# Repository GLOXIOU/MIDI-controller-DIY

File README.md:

# MIDI-controller-DIY

A DIY project for a MIDI controller designed to control lights, featuring knobs, faders, and buttons.

The project is designed to manage stage lighting systems with up to 10 faders, including a master one, 20 keyboard keys, 10 potards, and 3 rotary encoders.

The goal is to not pay hundreds of dollars for an already existing product, and learn! MIDI controller DIY is also intended to be a hardware platform for a future open-source lighting-control system.

---

## Features

* 20 usable keyboard keys
* 10 faders
* 10 potards
* 3 rotary encoders
* USB-C Output
* Compatibility with all lighting control systems via MIDI
* You can also use it as an instrument or anything else
* Compact and portable design
* Designed for DIY assembly and reproduction
* Low-cost hardware

And the design is made to be upgradable/updatable easily if necessary, so it will be able to last over time.

---

## Architecture

The ESP32-S3 is the central processor of the system. It handles USB-C communication and MIDI processing. To connect the ESP32 with all of the 43 components, there are 2 MUX units at the right of the box. 43 buttons, faders, etc., are fully customizable and you can use them as you want.

---

## Hardware and BOM

The current design uses the following main components:

| Component | Quantity | Price |
| --- | --- | --- |
| [Kailh Choc V1 1350](https://fr.aliexpress.com/item/1005012826040037.html?spm=a2g0o.cart.0.0.478d378dYODNq0&mp=1&pdp_npi=6%40dis%21USD%21USD%205.36%21USD%204.93%21%21USD%204.93%21%21%21%40210384a717913205885618903e10fc%2112000059425505100%21ct%21FR%218054027548%21%212%210%21&gatewayAdapt=glo2fra) | 20 | 9.86$ |
| [RV09 B10K 9 mm vertical](https://fr.aliexpress.com/item/1005005951601744.html?spm=a2g0o.productlist.main.2.6a013a5dBfqj0c&algo_pvid=9dd7ff78-7cef-4815-a249-9f4bb1d433f4&algo_exp_id=9dd7ff78-7cef-4815-a249-9f4bb1d433f4-1&pdp_ext_f=%7B%22order%22%3A%22197%22%2C%22eval%22%3A%221%22%2C%22fromPage%22%3A%22search%22%7D&pdp_npi=6%40dis%21USD%217.66%217.66%21%21%2151.02%2151.02%21%4021613be817921531317277993e10c3%2112000034999053530%21sea%21FR%218054027548%21X%211%210%21n_tag%3A-29911%3Bd%3A8484f755%3Bm03_new_user%3A-29895&curPageLogUid=b76fqSVCkx9n&utparam-url=scene%3Asearch%7Cquery_from%3A%7Cx_object_id%3A1005005951601744%7C_p_origin_prod%3A) | 10 | 7.90$ |
| [EC11 through-hole with push-button, 20 mm shaft](https://fr.aliexpress.com/item/1005009889978797.html?spm=a2g0o.cart.0.0.478d378dYODNq0&mp=1&pdp_npi=6%40dis%21USD%21USD%205.88%21USD%202.68%21%21USD%202.68%21%21%21%40210384a717913207470334482e10fc%2112000050490958429%21ct%21FR%218054027548%21%212%210%21&gatewayAdapt=glo2fra) | 3 | 5.36$ |
| [CD4067BE in DIP-24](https://fr.aliexpress.com/item/1005011580802574.html?spm=a2g0o.cart.0.0.478d378dYODNq0&mp=1&pdp_npi=6%40dis%21USD%21USD%206.69%21USD%206.69%21%21USD%206.69%21%21%21%40210384a717913207470334482e10fc%2112000055976316177%21ct%21FR%218054027548%21%211%210%21&gatewayAdapt=glo2fra) | 2 | 6.69$ |
| [1N4148 diodes](https://fr.aliexpress.com/item/4000142272546.html?spm=a2g0o.cart.0.0.478d378dYODNq0&mp=1&pdp_npi=6%40dis%21USD%21USD+1.64%21USD+1.64%21%21USD+1.64%21%21%21%40210384a717913207470334482e10fc%2110000000428321629%21ct%21FR%218054027548%21%211%210%21&pdp_ext_f=%7B%22cart2PdpParams%22%3A%7B%22pdpBusinessMode%22%3A%22retail%22%7D%7D&gatewayAdapt=glo2fra) | 20 | 1.64$ |
| [faders SC6021N 10k](https://fr.aliexpress.com/item/1005007799302164.html?spm=a2g0o.productlist.main.1.25616b84d4WSxL&algo_pvid=9953769d-b040-40bf-b6fd-b3c135a11ea9&algo_exp_id=9953769d-b040-40bf-b6fd-b3c135a11ea9-0&pdp_ext_f=%7B%22order%22%3A%22247%22%2C%22spu_best_type%22%3A%22price%22%2C%22eval%22%3A%221%22%2C%22fromPage%22%3A%22search%22%7D&pdp_npi=6%40dis%21USD%212.25%212.25%21%21%2115.00%2115.00%21%400b88486a17915615343565643e0f22%2112000042240271501%21sea%21FR%218054027548%21X%211%210%21n_tag%3A-29911%3Bd%3A8484f755%3Bm03_new_user%3A-29895&curPageLogUid=HQigGaQEblGd&utparam-url=scene%3Asearch%7Cquery_from%3A%7Cx_object_id%3A1005007799302164%7C_p_origin_prod%3A) | 10 | 9$ |
| [ESP32-S3 N16R8](https://fr.aliexpress.com/item/1005008809316571.html?spm=a2g0o.cart.0.0.478d378dYODNq0&mp=1&pdp_npi=6%40dis%21USD%21USD+8.02%21USD+8.02%21%21USD+8.02%21%21%21%40210384a717913207470334482e10fc%2112000046760012013%21ct%21FR%218054027548%21%211%210%21&pdp_ext_f=%7B%22cart2PdpParams%22%3A%7B%22pdpBusinessMode%22%3A%22retail%22%7D%7D&gatewayAdapt=glo2fra) | 1 | 8.02$ |
| [Knobs cap](https://fr.aliexpress.com/item/1005012925297636.html?spm=a2g0o.productlist.main.3.703f7c3epPU0Mz&algo_pvid=4c36b13e-f743-447c-8d31-d169bc98973d&algo_exp_id=4c36b13e-f743-447c-8d31-d169bc98973d-2&pdp_ext_f=%7B%22order%22%3A%2243%22%2C%22spu_best_type%22%3A%22price%22%2C%22eval%22%3A%221%22%2C%22fromPage%22%3A%22search%22%7D&pdp_npi=6%40dis%21USD%211.88%212.68%21%21%2112.52%2117.86%21%40210384a717915626045184749e0d20%2112000059797212246%21sea%21FR%218054027548%21X%211%210%21n_tag%3A-29911%3Bd%3A8484f755%3Bm03_new_user%3A-29895&curPageLogUid=mtFiF5q8pKs0&utparam-url=scene%3Asearch%7Cquery_from%3A%7Cx_object_id%3A1005012925297636%7C_p_origin_prod%3A) | 10 | 2.68$ |
| [PCB](https://jlcpcb.com/) | 1 | 16,60$ |
| [Lowprofile keycaps](https://fr.aliexpress.com/item/1005006624568390.html?spm=a2g0o.productlist.main.39.7ada7cc1xmwatk&algo_pvid=869ea550-58a6-4ce8-a4f5-cac4802f06d0&algo_exp_id=869ea550-58a6-4ce8-a4f5-cac4802f06d0-36&pdp_ext_f=%7B%22order%22%3A%2288%22%2C%22eval%22%3A%221%22%2C%22fromPage%22%3A%22search%22%7D&pdp_npi=6%40dis%21USD%218.67%218.67%21%21%2157.76%2157.76%21%402103849717915626622064135e13a7%2112000037855001108%21sea%21FR%218054027548%21X%211%210%21n_tag%3A-29911%3Bd%3A8484f755%3Bm03_new_user%3A-29895&curPageLogUid=p3pCjUj8SJOC&utparam-url=scene%3Asearch%7Cquery_from%3A%7Cx_object_id%3A1005006624568390%7C_p_origin_prod%3A) | 20 | 17.34$ |
| Total | --- | 85.09$ |

The complete component list is available in [BOM.csv](BOM.csv).

---

## Processing and memory

I selected the ESP32-S3 because the project requires a bit of processing power for MIDI handling, though not a huge amount. That’s why it’s better suited for the task than a Raspberry Pi.

It is responsible for:

* MIDI processing
* USB-C Output
* 43 component inputs

All the data, saves, and other settings are stored in the internal storage system of the ESP32.

---

## MIDI

The MIDI controller is designed to support lighting control software like grandMA onPC, QLC+, or others via standard MIDI remote commands.

Each hardware input reads multiple analog faders, push buttons, and encoders through multiplexers or direct GPIO pins on the ESP32.

Standard USB-MIDI and serial communication protocols are used, handled by the hardware USB/UART interfaces on the microcontroller.

The MIDI data rate operates at standard MIDI baud rates or high-speed USB-MIDI.

For example, moving a physical fader transmits a Control Change (CC) message to precisely control lighting playback levels in software.

---

## Components and enclosure

There is a PCB in this project because it's required. Here are all the components included:

* ESP32-S3 x1
* MUX CD4067BE in DIP-24 x2
* Kailh Choc V1 1350 x20
* RV09 B10K 9 mm vertical x10
* EC11 through-hole with push-button x3
* faders SC6021N B10K x10

Here's a screenshot of the PCB with some of the components:

The PCB file is [here](3D-files/PCB.step).
And you can modify it using KiCad with [this](KiCad%20-%20MIDI-controller) folder.

The case is 283mm x 250mm x 60mm, and is designed to perfectly house all components, be easy to install, not take up much space, and be durable.

Here's a look at it:

Assembly file: [assembly-Midi-controller-DIY.step](3D-files/assembly-Midi-controller-DIY.step)  
Print file: [to print](3D-files/to%20print/)

---

## Estimated cost

The current estimate is $85.09 of components.
This does not include assembly, enclosure parts, future design changes, or the print filament that I already have.

---

## Project journal

The development process is documented in [JOURNAL.md](JOURNAL.md).

It includes in-depth design, configuration, part of the code, enclosure design, BOM creation, and the problems encountered during development.

---

## Inspiration and credits

The MIDI Controller DIY project was inspired by the GrandMa Wing.

The MIDI Controller DIY is an independent design developed from this inspiration.

Credits:
* GrandMa Wing — inspiration for the project concept and overall goal of creating an affordable MIDI interface.
* GrabCAD community — some 3D component models were used as reference geometry for the CAD assembly. The original authors retain ownership of their respective models:
  * ESP32-S3
  * MUX CD4067BE in DIP-24
  * Kailh Choc V1 1350
  * RV09 B10K 9 mm vertical
  * EC11 through-hole with push-button
  * faders SC1009G B10K

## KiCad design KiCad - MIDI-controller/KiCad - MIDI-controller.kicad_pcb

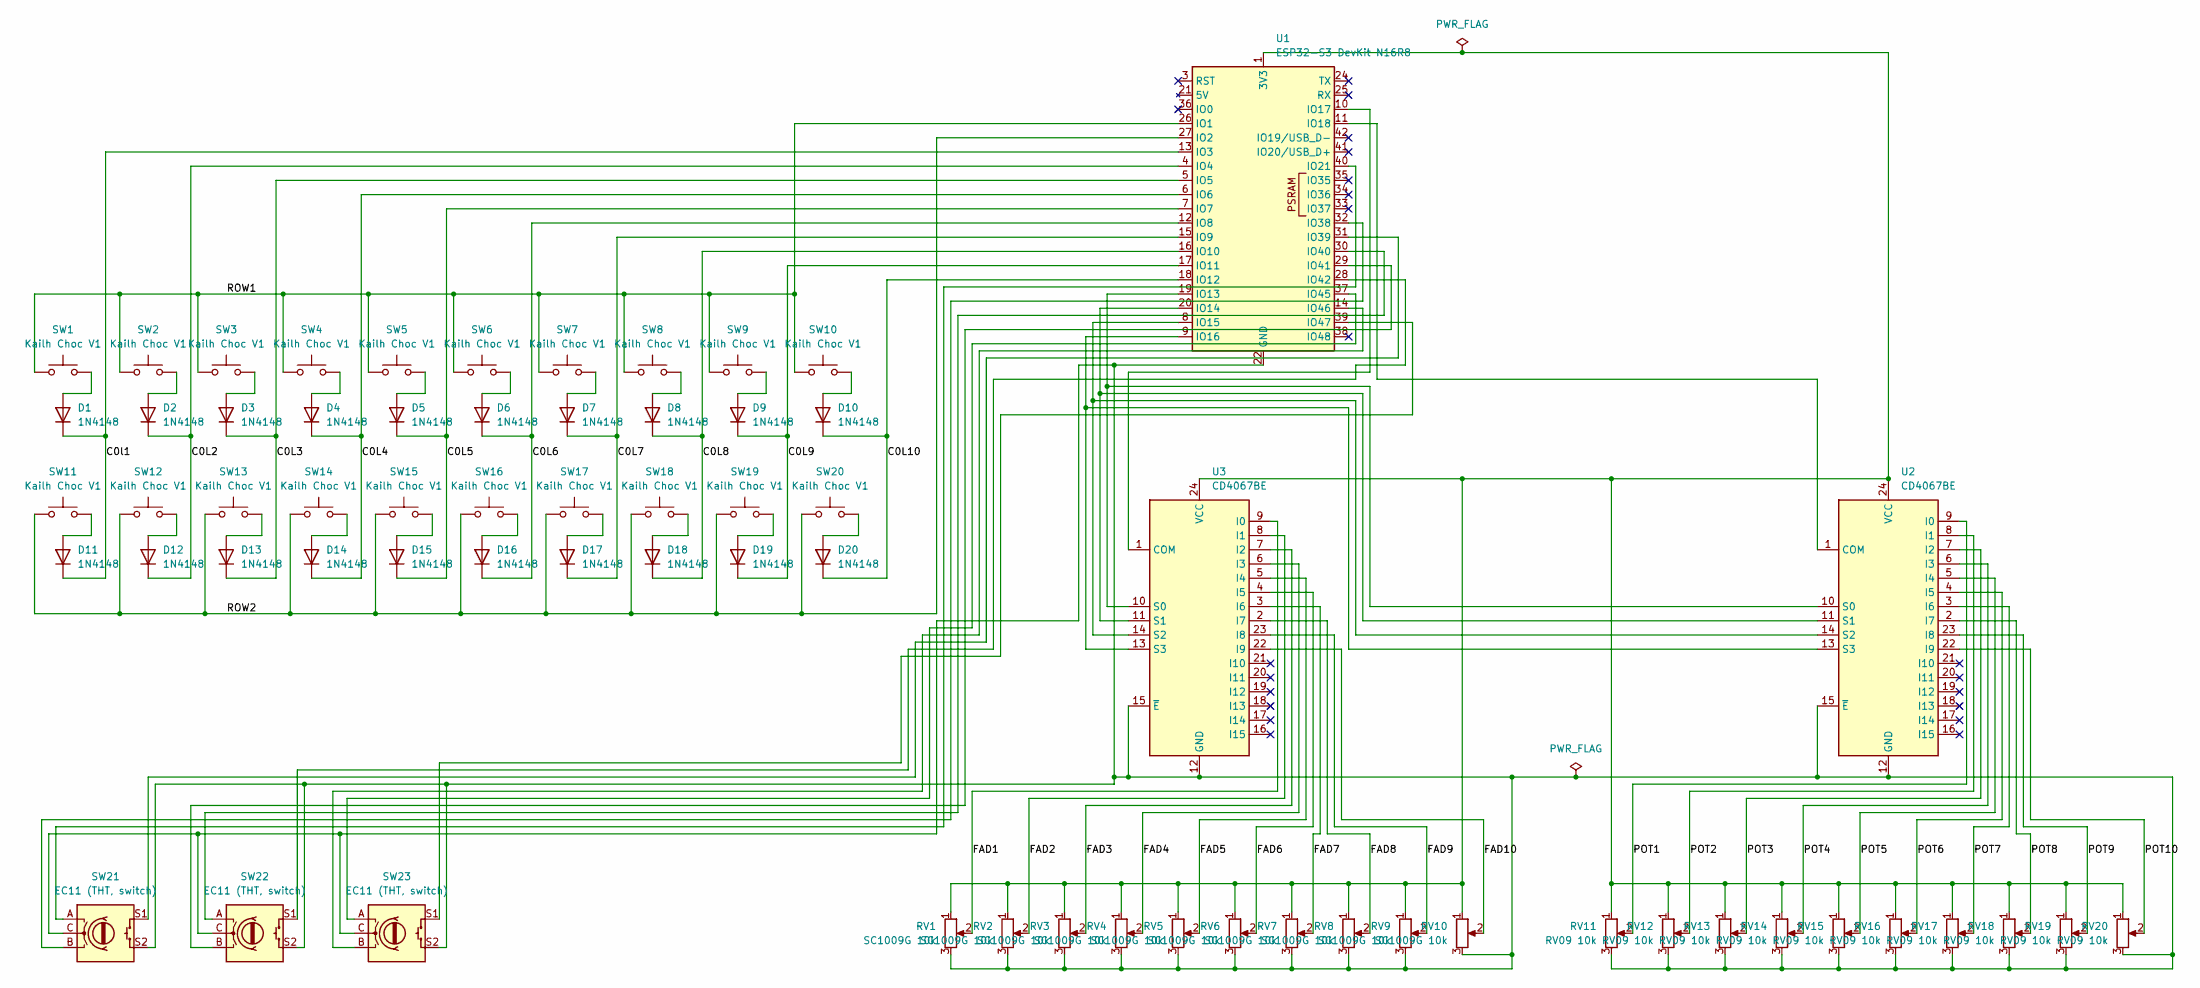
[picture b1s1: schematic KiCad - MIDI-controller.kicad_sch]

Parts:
D1, D2, D3, D4, D5, D6, D7, D8, D9, D10, D11, D12, D13, D14, D15, D16, D17, D18, D19, D20: 1N4148; D_DO-35_SOD27_P7.62mm_Horizontal
RV1, RV2, RV3, RV4, RV5, RV6, RV7, RV8, RV9, RV10: SC1009G 10k; PinHeader_1x03_P2.54mm_Vertical
RV11, RV12, RV13, RV14, RV15, RV16, RV17, RV18, RV19, RV20: RV09 10k; Potentiometer_Bourns_PTV09A-1_Single_Vertical
SW1, SW2, SW3, SW4, SW5, SW6, SW7, SW8, SW9, SW10, SW11, SW12, SW13, SW14, SW15, SW16, SW17, SW18, SW19, SW20: Kailh Choc V1; SW_Kailh_Choc_V1_1.00u
SW21, SW22, SW23: EC11 (THT, switch); RotaryEncoder_Alps_EC11E-Switch_Vertical_H20mm
U1: ESP32-S3 DevKit N16R8; ESP32-S3-DevKitC-1_44P_W25.4mm
U2, U3: CD4067BE; DIP-24_W15.24mm

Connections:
/C0L2: D2.1 (K), D12.1 (K), U1.4 (IO4)
/C0L3: D3.1 (K), D13.1 (K), U1.5 (IO5)
/C0L4: D4.1 (K), D14.1 (K), U1.6 (IO6)
/C0L5: D5.1 (K), D15.1 (K), U1.7 (IO7)
/C0L6: D6.1 (K), D16.1 (K), U1.12 (IO8)
/C0L7: D7.1 (K), D17.1 (K), U1.15 (IO9)
/C0L8: D8.1 (K), D18.1 (K), U1.16 (IO10)
/C0L9: D9.1 (K), D19.1 (K), U1.17 (IO11)
/C0L10: D10.1 (K), D20.1 (K), U1.18 (IO12)
/C0l1: D1.1 (K), D11.1 (K), U1.13 (IO3)
/FAD1: RV1.2, U3.9 (I0)
/FAD2: RV2.2, U3.8 (I1)
/FAD3: RV3.2, U3.7 (I2)
/FAD4: RV4.2, U3.6 (I3)
/FAD5: RV5.2, U3.5 (I4)
/FAD6: RV6.2, U3.4 (I5)
/FAD7: RV7.2, U3.3 (I6)
/FAD8: RV8.2, U3.2 (I7)
/FAD9: RV9.2, U3.23 (I8)
/FAD10: RV10.2, U3.22 (I9)
/POT1: RV11.2, U2.9 (I0)
/POT2: RV12.2, U2.8 (I1)
/POT3: RV13.2, U2.7 (I2)
/POT4: RV14.2, U2.6 (I3)
/POT5: RV15.2, U2.5 (I4)
/POT6: RV16.2, U2.4 (I5)
/POT7: RV17.2, U2.3 (I6)
/POT8: RV18.2, U2.2 (I7)
/POT9: RV19.2, U2.23 (I8)
/POT10: RV20.2, U2.22 (I9)
/ROW1: SW1.1, SW2.1, SW3.1, SW4.1, SW5.1, SW6.1, SW7.1, SW8.1, SW9.1, SW10.1, U1.26 (IO1)
/ROW2: SW11.1, SW12.1, SW13.1, SW14.1, SW15.1, SW16.1, SW17.1, SW18.1, SW19.1, SW20.1, U1.27 (IO2)
unnamed: D1.2 (A), SW1.2
unnamed: D2.2 (A), SW2.2
unnamed: D3.2 (A), SW3.2
unnamed: D4.2 (A), SW4.2
unnamed: D5.2 (A), SW5.2
unnamed: D6.2 (A), SW6.2
unnamed: D7.2 (A), SW7.2
unnamed: D8.2 (A), SW8.2
unnamed: D9.2 (A), SW9.2
unnamed: D10.2 (A), SW10.2
unnamed: D11.2 (A), SW11.2
unnamed: D12.2 (A), SW12.2
unnamed: D13.2 (A), SW13.2
unnamed: D14.2 (A), SW14.2
unnamed: D15.2 (A), SW15.2
unnamed: D16.2 (A), SW16.2
unnamed: D17.2 (A), SW17.2
unnamed: D18.2 (A), SW18.2
unnamed: D19.2 (A), SW19.2
unnamed: D20.2 (A), SW20.2
unnamed: U1.19 (IO13), U2.10 (S0), U3.10 (S0)
unnamed: U1.20 (IO14), U2.11 (S1), U3.11 (S1)
unnamed: U1.8 (IO15), U2.14 (S2), U3.14 (S2)
unnamed: U1.9 (IO16), U2.13 (S3), U3.13 (S3)
unnamed: U1.10 (IO17), U3.1 (COM)
unnamed: U1.11 (IO18), U2.1 (COM)
unnamed: SW21.A, U1.40 (IO21)
unnamed: SW21.B, U1.32 (IO38)
unnamed: SW21.S1, U1.31 (IO39)
unnamed: SW22.A, U1.30 (IO40)
unnamed: SW22.B, U1.29 (IO41)
unnamed: SW22.S1, U1.28 (IO42)
unnamed: SW23.A, U1.37 (IO45)
unnamed: SW23.B, U1.14 (IO46)
unnamed: SW23.S1, U1.39 (IO47)
unnamed: RV1.3, RV2.3, RV3.3, RV4.3, RV5.3, RV6.3, RV7.3, RV8.3, RV9.3, RV10.3, RV11.3, RV12.3, RV13.3, RV14.3, RV15.3, RV16.3, RV17.3, RV18.3, RV19.3, RV20.3, SW21.C, SW21.S2, SW22.C, SW22.S2, SW23.C, SW23.S2, U1.22 (GND), U1.23 (GND), U1.43 (GND), U1.44 (GND), U2.12 (GND), U2.15 (~E), U3.12 (GND), U3.15 (~E)
unnamed: RV1.1, RV2.1, RV3.1, RV4.1, RV5.1, RV6.1, RV7.1, RV8.1, RV9.1, RV10.1, RV11.1, RV12.1, RV13.1, RV14.1, RV15.1, RV16.1, RV17.1, RV18.1, RV19.1, RV20.1, U1.1 (3V3), U1.2 (3V3), U2.24 (VCC), U3.24 (VCC)

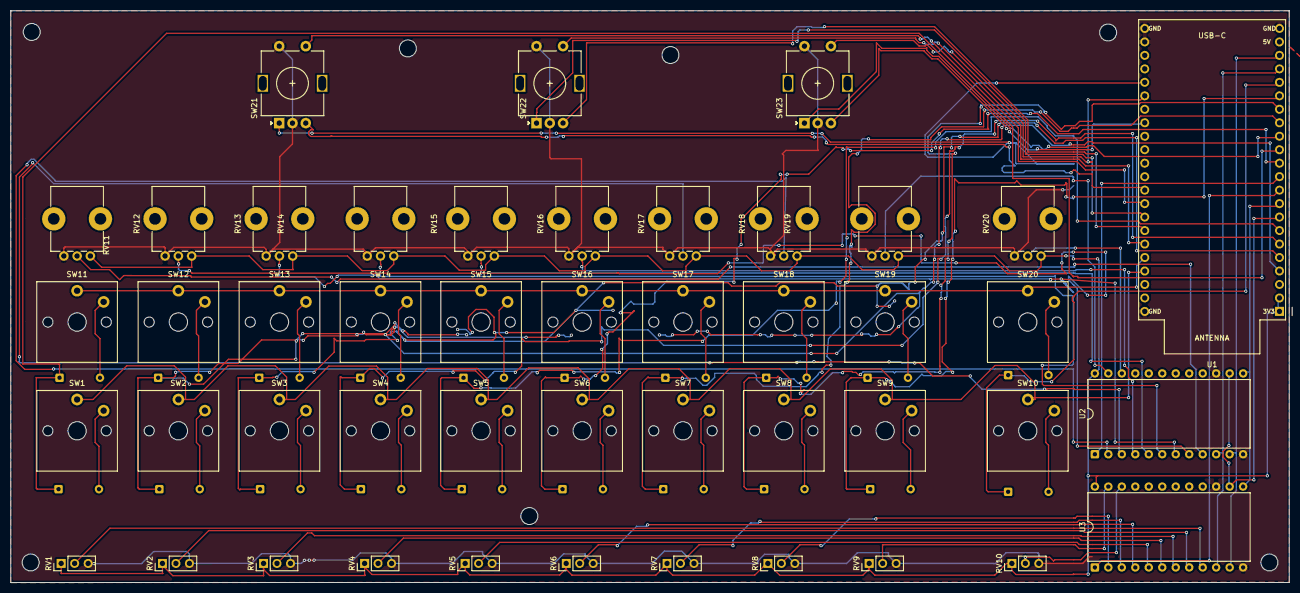
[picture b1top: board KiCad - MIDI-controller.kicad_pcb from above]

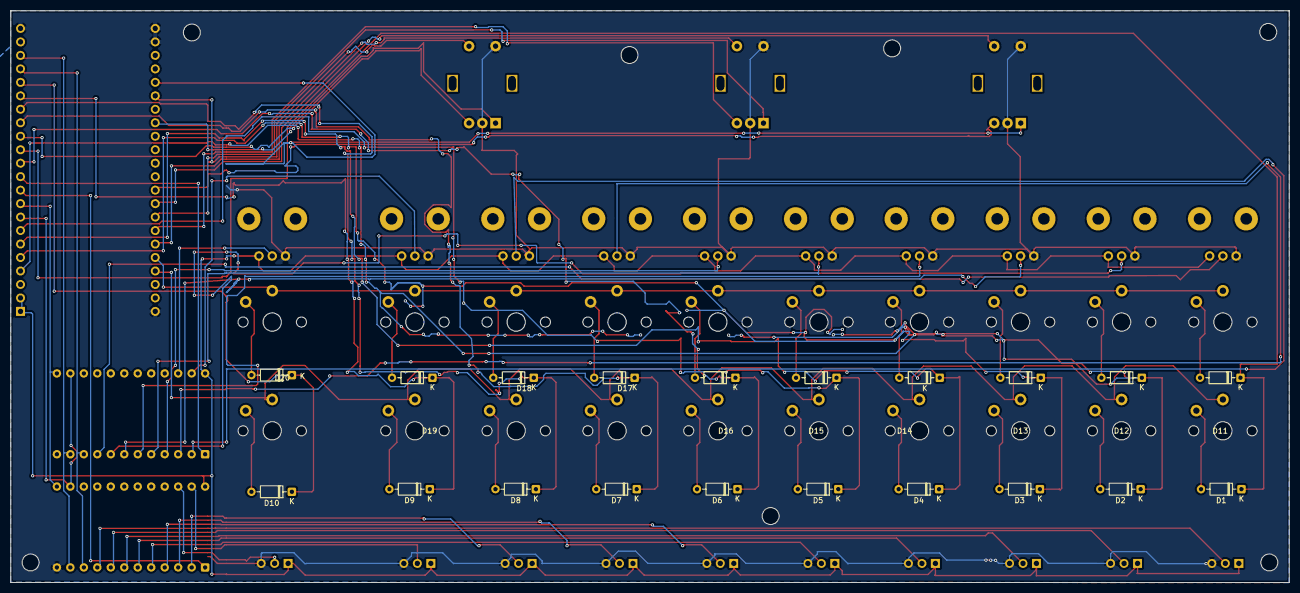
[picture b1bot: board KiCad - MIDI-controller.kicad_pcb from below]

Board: 2 copper layers, 241.0 x 107.8 mm, 73 parts (20 on the bottom side), 69 nets.

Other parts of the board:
H1, H2, H3, H4, H5, H6, H7: M3; MountingHole_3.2mm_M3
